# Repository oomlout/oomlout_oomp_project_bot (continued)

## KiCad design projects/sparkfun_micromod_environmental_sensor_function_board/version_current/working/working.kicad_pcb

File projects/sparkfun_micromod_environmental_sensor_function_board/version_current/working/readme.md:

# MicroMod_Environmental_Sensor_Function_Board by sparkfun  
This is a harvested standardized copy of a project from github.  
The original project can be found at:  
https://github.com/sparkfun/MicroMod_Environmental_Sensor_Function_Board  
Please consult that link for additional, details, files, and license information.  
Note: It was auto harvested and if the original repo had more than one board file or anything out of the ordinary the files here are likely not representative.

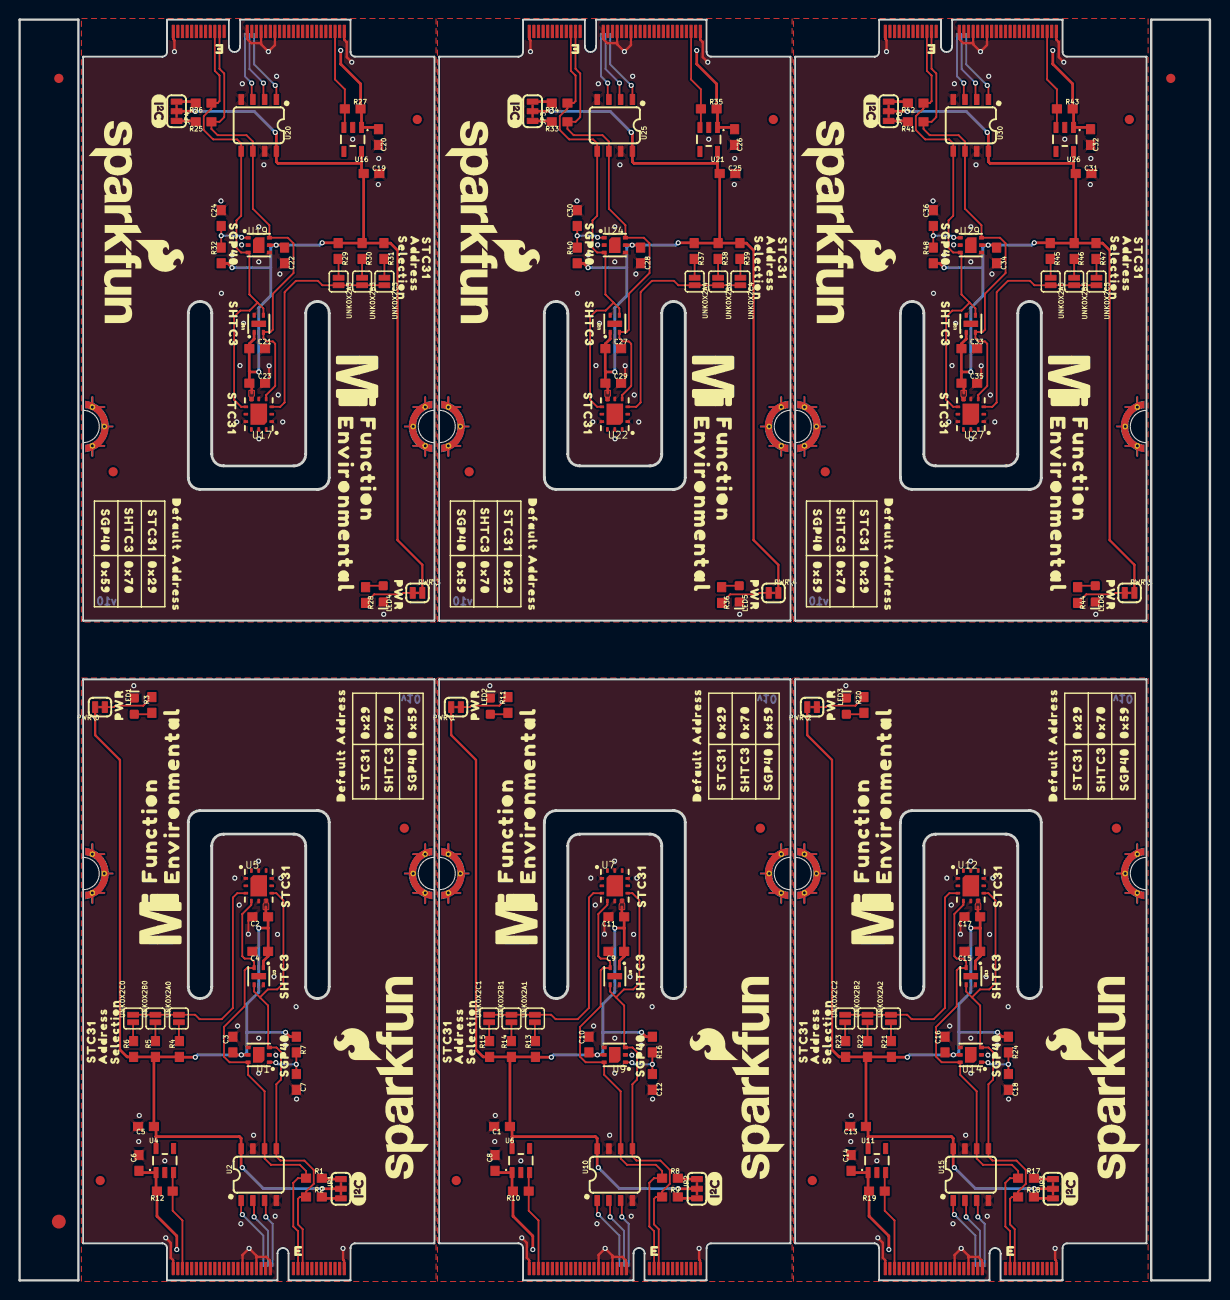
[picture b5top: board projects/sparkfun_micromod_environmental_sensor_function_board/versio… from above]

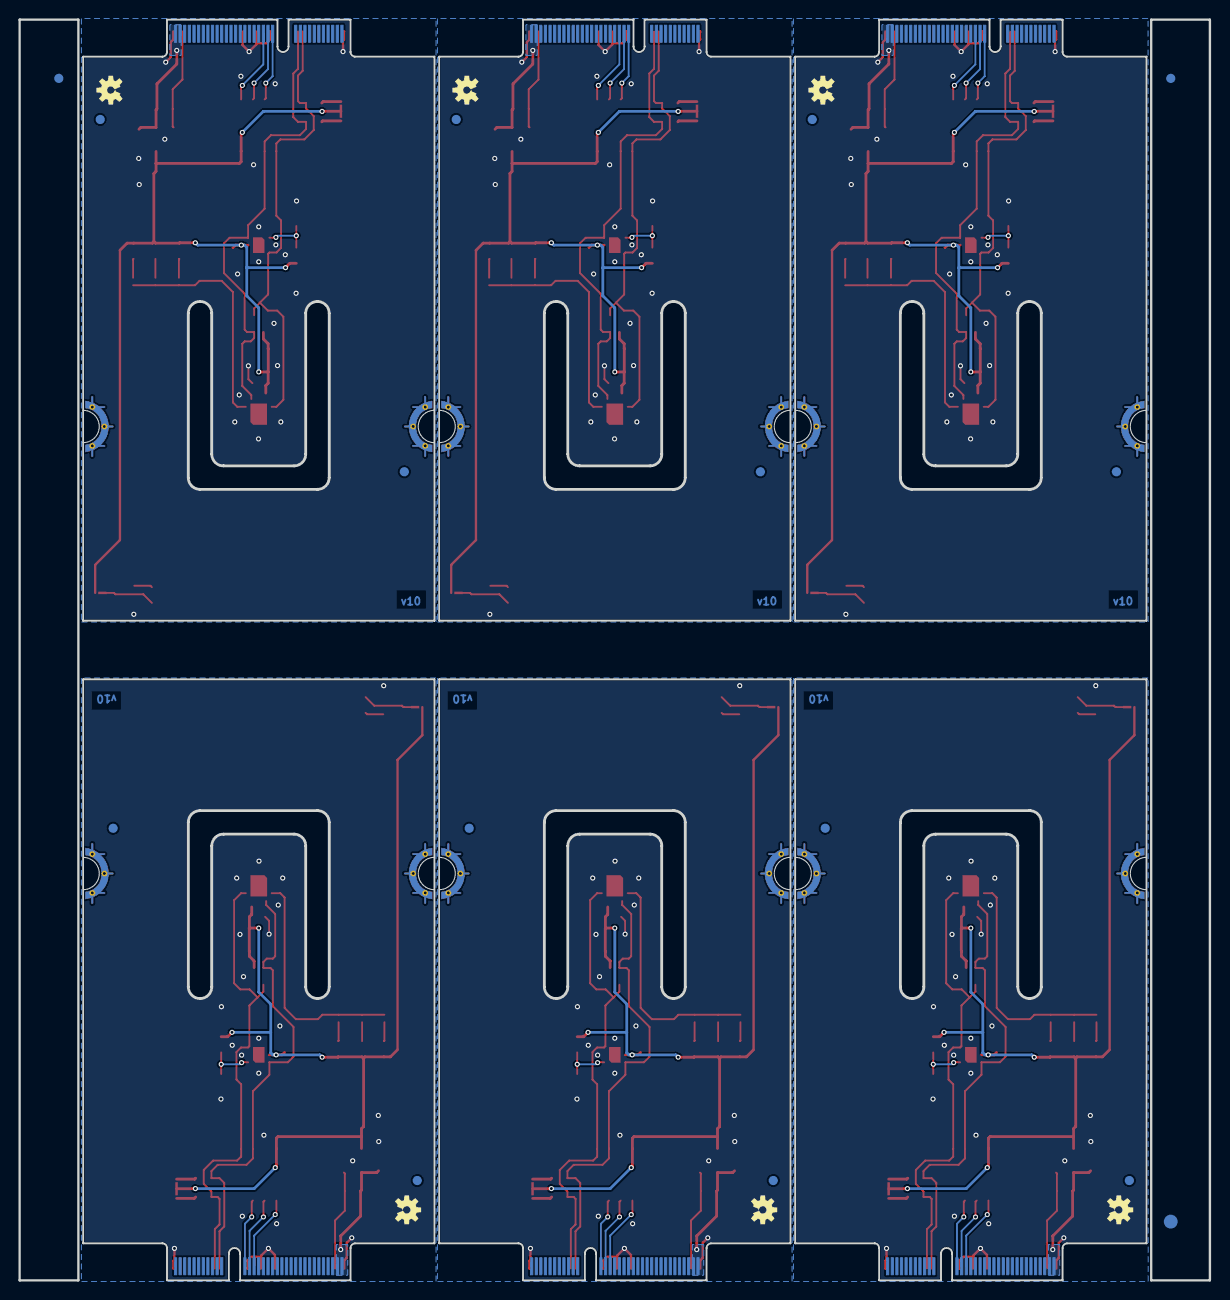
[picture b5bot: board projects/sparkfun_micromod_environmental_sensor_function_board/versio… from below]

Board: 2 copper layers, 128.7 x 136.3 mm, 330 parts (21 on the bottom side), 108 nets.

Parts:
C1, C2, C5, C6, C7, C8, C11, C12, C13, C14, C17, C18, C19, C20, C23, C24, C25, C26, C29, C30, C31, C32, C35, C36: 1.0uF; 0603
C3, C4, C9, C10, C15, C16, C21, C22, C27, C28, C33, C34: 0.1uF; 0603
E$1, E$2, E$3, E$4: FIDUCIAL-1X2
E$5, E$6: FIDUCIAL-1.5X3
FD1, FD2, FD3, FD4, FD5, FD6, FD7, FD8, FD9, FD10, FD11, FD12, FD13, FD14, FD15, FD16, FD17, FD18, FD19, FD20, FD21, FD22, FD23, FD24: FIDUCIAL1X2; FIDUCIAL-1X2
J1, J2, J3, J4, J5, J6: MICROMOD_STANDARD; M.2-CARD-E-22_FUNCTION_STANDARD
JP1, JP2, JP3, JP4, JP5, JP6: JUMPER-SMT_3_2-NC_TRACE_SILK; SMT-JUMPER_3_2-NC_TRACE_SILK
LED1, LED2, LED3, LED4, LED5, LED6: RED; LED-0603
LOGO1, LOGO3, LOGO5, LOGO7, LOGO9, LOGO11: SFE_LOGO_NAME_FLAME.2_INCH; SFE_LOGO_NAME_FLAME_.2
LOGO2, LOGO4, LOGO6, LOGO8, LOGO10, LOGO12: OSHW-LOGOS; OSHW-LOGO-S
PWR\0, PWR\1, PWR\2, PWR\3, PWR\4, PWR\5: JUMPER-SMT_2_NC_TRACE_SILK; SMT-JUMPER_2_NC_TRACE_SILK
R1, R2, R8, R9, R17, R18, R25, R26, R33, R34, R41, R42: 4.7k; 0603
R3, R6, R11, R15, R20, R23, R28, R31, R36, R39, R44, R47: 1k; 0603
R4, R13, R21, R29, R37, R45: 10k; 0603
R5, R14, R22, R30, R38, R46: 3.3k; 0603
R7, R16, R24, R32, R40, R48: 4.7; 0603
R10, R12, R19, R27, R35, R43: 100k; 0603
U1, U9, U14, U19, U24, U29: SGP40
U2, U10, U15, U20, U25, U30: EEPROM; SO08
U3, U8, U13, U18, U23, U28: SHTC3
U4, U6, U11, U16, U21, U26: 3.3V; SOT23-5
U5, U7, U12, U17, U22, U27: STC31
U$1, U$23, U$45, U$67, U$89, U$111: #0X2A#21
U$2, U$24, U$46, U$68, U$90, U$112: #0X2B#21
U$3, U$25, U$47, U$69, U$91, U$113: #0X2C#21
U$4, U$26, U$48, U$70, U$92, U$114: PWR321541
U$5, U$27, U$49, U$71, U$93, U$115: FUNCTION524
U$6, U$28, U$50, U$72, U$94, U$116: ENVIRONMENTAL526
U$7, U$29, U$51, U$73, U$95, U$117: MICROMOD_MI_LOGO_1
U$8, U$30, U$52, U$74, U$96, U$118: I2C
U$9, U$15, U$35, U$42, U$57, U$64, U$79, U$86, U$101, U$108, U$123, U$130: ADDRESS40313505
U$10, U$39, U$61, U$83, U$105, U$127: 0X2940313520
U$11, U$18, U$31, U$38, U$53, U$60, U$75, U$82, U$97, U$104, U$119, U$126: SGP40313503
U$12, U$17, U$32, U$37, U$54, U$59, U$76, U$81, U$98, U$103, U$120, U$125: SHTC3501
U$13, U$16, U$22, U$33, U$36, U$44, U$55, U$58, U$66, U$77, U$80, U$88, U$99, U$102, U$110, U$121, U$124, U$132: STC313502
U$14, U$34, U$56, U$78, U$100, U$122: DEFAULT40313504
U$19, U$40, U$62, U$84, U$106, U$128: 0X5940313520
U$20, U$41, U$63, U$85, U$107, U$129: 0X7040313520
U$21, U$43, U$65, U$87, U$109, U$131: SELECTION40313506
UNK0X2A0, UNK0X2A1, UNK0X2A2, UNK0X2A3, UNK0X2A4, UNK0X2A5, UNK0X2B0, UNK0X2B1, UNK0X2B2, UNK0X2B3, UNK0X2B4, UNK0X2B5, UNK0X2C0, UNK0X2C1, UNK0X2C2, UNK0X2C3, UNK0X2C4, UNK0X2C5: JUMPER-SMT_2_NO_SILK; SMT-JUMPER_2_NO_SILK

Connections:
3.3V: C2.1, C3.1, C4.1, C5.1, JP1.2, PWR\0.2, R4.1, R5.1, R6.1, R7.1, U1.5, U2.8, U3.1, U4.5, U5.6
3.3V1: C1.1, C9.1, C10.1, C11.1, JP2.2, PWR\1.2, R13.1, R14.1, R15.1, R16.1, U6.5, U7.6, U8.1, U9.5, U10.8
3.3V2: C13.1, C15.1, C16.1, C17.1, JP3.2, PWR\2.2, R21.1, R22.1, R23.1, R24.1, U11.5, U12.6, U13.1, U14.5, U15.8
3.3V3: C19.1, C21.1, C22.1, C23.1, JP4.2, PWR\3.2, R29.1, R30.1, R31.1, R32.1, U16.5, U17.6, U18.1, U19.5, U20.8
3.3V4: C25.1, C27.1, C28.1, C29.1, JP5.2, PWR\4.2, R37.1, R38.1, R39.1, R40.1, U21.5, U22.6, U23.1, U24.5, U25.8
3.3V5: C31.1, C33.1, C34.1, C35.1, JP6.2, PWR\5.2, R45.1, R46.1, R47.1, R48.1, U26.5, U27.6, U28.1, U29.5, U30.8
A0: J1.36, U2.1
A1: J1.34, U2.2
A2: J1.32, U2.3
A3: J2.36, U10.1
A4: J2.32, U10.3
A5: J2.34, U10.2
A6: J3.36, U15.1
A7: J3.32, U15.3
A8: J3.34, U15.2
A9: J4.36, U20.1
A10: J4.32, U20.3
A11: J4.34, U20.2
A12: J5.36, U25.1
A13: J5.32, U25.3
A14: J5.34, U25.2
A15: J6.36, U30.1
A16: J6.32, U30.3
A17: J6.34, U30.2
ADDR: U5.3, UNK0X2A0.2, UNK0X2B0.2, UNK0X2C0.2
ADDR1: U7.3, UNK0X2A1.2, UNK0X2B1.2, UNK0X2C1.2
ADDR2: U12.3, UNK0X2A2.2, UNK0X2B2.2, UNK0X2C2.2
ADDR3: U17.3, UNK0X2A3.2, UNK0X2B3.2, UNK0X2C3.2
ADDR4: U22.3, UNK0X2A4.2, UNK0X2B4.2, UNK0X2C4.2
ADDR5: U27.3, UNK0X2A5.2, UNK0X2B5.2, UNK0X2C5.2
EN: J1.71, R12.1, U4.3
EN1: J2.71, R10.1, U6.3
EN2: J3.71, R19.1, U11.3
EN3: J4.71, R27.1, U16.3
EN4: J5.71, R35.1, U21.3
EN5: J6.71, R43.1, U26.3
GND: C2.2, C3.2, C4.2, C5.2, C6.2, C7.2, J1.1, J1.33, J1.39, J1.45, J1.75, J1.GND1, J1.GND2, J1.GND3, J1.GND4, J1.GND5, J1.GND6, LED1.C, U1.2, U1.4, U1.DIEPAD, U2.4, U2.7, U3.4, U3.5, U4.2, U5.1, U5.5, U5.9, U5.11, U5.DIEPAD
GND1: C1.2, C8.2, C9.2, C10.2, C11.2, C12.2, J2.1, J2.33, J2.39, J2.45, J2.75, J2.GND1, J2.GND2, J2.GND3, J2.GND4, J2.GND5, J2.GND6, LED2.C, U6.2, U7.1, U7.5, U7.9, U7.11, U7.DIEPAD, U8.4, U8.5, U9.2, U9.4, U9.DIEPAD, U10.4, U10.7
GND2: C13.2, C14.2, C15.2, C16.2, C17.2, C18.2, J3.1, J3.33, J3.39, J3.45, J3.75, J3.GND1, J3.GND2, J3.GND3, J3.GND4, J3.GND5, J3.GND6, LED3.C, U11.2, U12.1, U12.5, U12.9, U12.11, U12.DIEPAD, U13.4, U13.5, U14.2, U14.4, U14.DIEPAD, U15.4, U15.7
GND3: C19.2, C20.2, C21.2, C22.2, C23.2, C24.2, J4.1, J4.33, J4.39, J4.45, J4.75, J4.GND1, J4.GND2, J4.GND3, J4.GND4, J4.GND5, J4.GND6, LED4.C, U16.2, U17.1, U17.5, U17.9, U17.11, U17.DIEPAD, U18.4, U18.5, U19.2, U19.4, U19.DIEPAD, U20.4, U20.7
GND4: C25.2, C26.2, C27.2, C28.2, C29.2, C30.2, J5.1, J5.33, J5.39, J5.45, J5.75, J5.GND1, J5.GND2, J5.GND3, J5.GND4, J5.GND5, J5.GND6, LED5.C, U21.2, U22.1, U22.5, U22.9, U22.11, U22.DIEPAD, U23.4, U23.5, U24.2, U24.4, U24.DIEPAD, U25.4, U25.7
GND5: C31.2, C32.2, C33.2, C34.2, C35.2, C36.2, J6.1, J6.33, J6.39, J6.45, J6.75, J6.GND1, J6.GND2, J6.GND3, J6.GND4, J6.GND5, J6.GND6, LED6.C, U26.2, U27.1, U27.5, U27.9, U27.11, U27.DIEPAD, U28.4, U28.5, U29.2, U29.4, U29.DIEPAD, U30.4, U30.7
unnamed: PWR\0.1, R3.2
unnamed: C7.1, R7.2, U1.1
unnamed: JP1.3, R1.2
unnamed: JP1.1, R2.2
unnamed: R4.2, UNK0X2A0.1
unnamed: R5.2, UNK0X2B0.1
unnamed: R6.2, UNK0X2C0.1
unnamed: LED2.A, R11.1
unnamed: PWR\1.1, R11.2
unnamed: LED1.A, R3.1
unnamed: R13.2, UNK0X2A1.1
unnamed: R14.2, UNK0X2B1.1
unnamed: R15.2, UNK0X2C1.1
unnamed: C12.1, R16.2, U9.1
unnamed: JP2.3, R8.2
unnamed: JP2.1, R9.2
unnamed: LED3.A, R20.1
unnamed: PWR\2.1, R20.2
unnamed: R21.2, UNK0X2A2.1
unnamed: R22.2, UNK0X2B2.1
unnamed: R23.2, UNK0X2C2.1
unnamed: C18.1, R24.2, U14.1
unnamed: JP3.3, R17.2
unnamed: JP3.1, R18.2
unnamed: LED4.A, R28.1
unnamed: PWR\3.1, R28.2
unnamed: R29.2, UNK0X2A3.1
unnamed: R30.2, UNK0X2B3.1
unnamed: R31.2, UNK0X2C3.1
unnamed: C24.1, R32.2, U19.1
unnamed: JP4.3, R25.2
unnamed: JP4.1, R26.2
unnamed: LED5.A, R36.1
unnamed: PWR\4.1, R36.2
unnamed: R37.2, UNK0X2A4.1
unnamed: R38.2, UNK0X2B4.1
unnamed: R39.2, UNK0X2C4.1
unnamed: C30.1, R40.2, U24.1
unnamed: JP5.3, R33.2
unnamed: JP5.1, R34.2
unnamed: LED6.A, R44.1
unnamed: PWR\5.1, R44.2
unnamed: R45.2, UNK0X2A5.1
unnamed: R46.2, UNK0X2B5.1
unnamed: R47.2, UNK0X2C5.1
unnamed: C36.1, R48.2, U29.1
unnamed: JP6.3, R41.2
unnamed: JP6.1, R42.2
SCL: J1.21, R1.1, U1.6, U2.6, U3.2, U5.4
SCL1: J2.21, R8.1, U7.4, U8.2, U9.6, U10.6
SCL2: J3.21, R17.1, U12.4, U13.2, U14.6, U15.6
SCL3: J4.21, R25.1, U17.4, U18.2, U19.6, U20.6
SCL4: J5.21, R33.1, U22.4, U23.2, U24.6, U25.6
SCL5: J6.21, R41.1, U27.4, U28.2, U29.6, U30.6
SDA: J1.19, R2.1, U1.3, U2.5, U3.3, U5.7
SDA1: J2.19, R9.1, U7.7, U8.3, U9.3, U10.5
SDA2: J3.19, R18.1, U12.7, U13.3, U14.3, U15.5
SDA3: J4.19, R26.1, U17.7, U18.3, U19.3, U20.5
SDA4: J5.19, R34.1, U22.7, U23.3, U24.3, U25.5
SDA5: J6.19, R42.1, U27.7, U28.3, U29.3, U30.5
VCC: C6.1, J1.72, J1.74, R12.2, U4.1
VCC1: C8.1, J2.72, J2.74, R10.2, U6.1
VCC2: C14.1, J3.72, J3.74, R19.2, U11.1
VCC3: C20.1, J4.72, J4.74, R27.2, U16.1
VCC4: C26.1, J5.72, J5.74, R35.2, U21.1
VCC5: C32.1, J6.72, J6.74, R43.2, U26.1

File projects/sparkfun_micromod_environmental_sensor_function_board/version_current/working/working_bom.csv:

"Id";"Designator";"Footprint";"Quantity";"Designation";"Supplier and ref";
1;"U$61,U$83,U$105,U$127,U$39,U$10";"0X2940313520";6;"";;;
2;"U$23,U$89,U$45,U$1,U$111,U$67";"#0X2A#21";6;"";;;
3;"U$95,U$51,U$29,U$7,U$73,U$117";"MICROMOD_MI_LOGO_1";6;"";;;
4;"U$38,U$97,U$31,U$119,U$75,U$11,U$60,U$126,U$18,U$53,U$82,U$104";"SGP40313503";12;"";;;
5;"R13,R45,R29,R21,R37,R4";"0603";6;"10k";;;
6;"PWR\3,PWR\1,PWR\2,PWR\5,PWR\0,PWR\4";"SMT-JUMPER_2_NC_TRACE_SILK";6;"JUMPER-SMT_2_NC_TRACE_SILK";;;
7;"U7,U27,U5,U12,U22,U17";"STC31";6;"STC31";;;
8;"FD12,FD17,FD20,FD5,FD16,FD13,FD21,FD9,FD4,FD24,FD1,FD8,FD19,FD7,FD2,FD23,FD15,FD10,FD3,FD11,FD14,FD6,FD18,FD22";"FIDUCIAL-1X2";24;"FIDUCIAL1X2";;;
9;"R25,R42,R18,R9,R1,R17,R33,R34,R2,R41,R26,R8";"0603";12;"4.7k";;;
10;"LED5,LED4,LED2,LED1,LED6,LED3";"LED-0603";6;"RED";;;
11;"R22,R46,R38,R30,R14,R5";"0603";6;"3.3k";;;
12;"C12,C25,C18,C13,C35,C7,C30,C17,C2,C23,C31,C26,C19,C6,C24,C14,C1,C36,C29,C11,C5,C20,C32,C8";"0603";24;"1.0uF";;;
13;"U$115,U$93,U$71,U$49,U$27,U$5";"FUNCTION524";6;"";;;
14;"U$58,U$80,U$22,U$55,U$88,U$44,U$121,U$33,U$102,U$36,U$124,U$13,U$132,U$66,U$110,U$77,U$99,U$16";"STC313502";18;"";;;
15;"U30,U15,U25,U2,U20,U10";"SO08";6;"EEPROM";;;
16;"U$112,U$68,U$90,U$46,U$24,U$2";"#0X2B#21";6;"";;;
17;"U$14,U$56,U$100,U$78,U$34,U$122";"DEFAULT40313504";6;"";;;
18;"U$72,U$28,U$6,U$50,U$116,U$94";"ENVIRONMENTAL526";6;"";;;
19;"U$103,U$76,U$32,U$120,U$17,U$54,U$125,U$98,U$81,U$59,U$37,U$12";"SHTC3501";12;"";;;
20;"U$9,U$123,U$15,U$86,U$35,U$57,U$108,U$130,U$42,U$79,U$101,U$64";"ADDRESS40313505";12;"";;;
21;"U4,U21,U16,U26,U11,U6";"SOT23-5";6;"3.3V";;;
22;"C4,C33,C3,C16,C10,C34,C22,C28,C15,C21,C9,C27";"0603";12;"0.1uF";;;
23;"JP1,JP4,JP2,JP6,JP5,JP3";"SMT-JUMPER_3_2-NC_TRACE_SILK";6;"JUMPER-SMT_3_2-NC_TRACE_SILK";;;
24;"UNK0X2A2,UNK0X2C4,UNK0X2A1,UNK0X2B5,UNK0X2B0,UNK0X2A5,UNK0X2A4,UNK0X2B2,UNK0X2B1,UNK0X2C1,UNK0X2C3,UNK0X2A0,UNK0X2C2,UNK0X2C0,UNK0X2B4,UNK0X2C5,UNK0X2B3,UNK0X2A3";"SMT-JUMPER_2_NO_SILK";18;"JUMPER-SMT_2_NO_SILK";;;
25;"R36,R11,R47,R28,R15,R44,R3,R31,R20,R6,R39,R23";"0603";12;"1k";;;
26;"U$30,U$74,U$52,U$8,U$118,U$96";"I2C";6;"";;;
27;"R10,R27,R35,R19,R12,R43";"0603";6;"100k";;;
28;"U$20,U$107,U$129,U$85,U$41,U$63";"0X7040313520";6;"";;;
29;"U1,U29,U9,U24,U14,U19";"SGP40";6;"SGP40";;;
30;"U$87,U$131,U$65,U$109,U$21,U$43";"SELECTION40313506";6;"";;;
31;"U3,U18,U28,U13,U8,U23";"SHTC3";6;"SHTC3";;;
32;"J1,J5,J6,J4,J2,J3";"M.2-CARD-E-22_FUNCTION_STANDARD";6;"MICROMOD_STANDARD";;;
33;"U$4,U$114,U$92,U$26,U$70,U$48";"PWR321541";6;"";;;
34;"U$47,U$3,U$25,U$113,U$69,U$91";"#0X2C#21";6;"";;;
35;"LOGO9,LOGO3,LOGO11,LOGO7,LOGO1,LOGO5";"SFE_LOGO_NAME_FLAME_.2";6;"SFE_LOGO_NAME_FLAME.2_INCH";;;
36;"R48,R40,R32,R24,R16,R7";"0603";6;"4.7";;;
37;"E$5,E$6";"FIDUCIAL-1.5X3";2;"";;;
38;"U$19,U$106,U$40,U$128,U$62,U$84";"0X5940313520";6;"";;;
39;"E$1,E$3,E$2,E$4";"FIDUCIAL-1X2";4;"";;;
40;"LOGO12,LOGO2,LOGO8,LOGO10,LOGO6,LOGO4";"OSHW-LOGO-S";6;"OSHW-LOGOS";;;

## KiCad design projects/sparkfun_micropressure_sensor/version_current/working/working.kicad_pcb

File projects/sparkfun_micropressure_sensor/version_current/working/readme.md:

# MicroPressure_Sensor by sparkfun  
This is a harvested standardized copy of a project from github.  
The original project can be found at:  
https://github.com/sparkfun/MicroPressure_Sensor  
Please consult that link for additional, details, files, and license information.  
Note: It was auto harvested and if the original repo had more than one board file or anything out of the ordinary the files here are likely not representative.

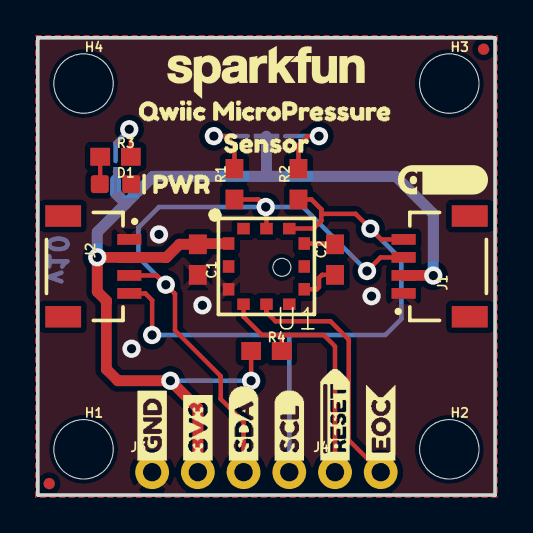
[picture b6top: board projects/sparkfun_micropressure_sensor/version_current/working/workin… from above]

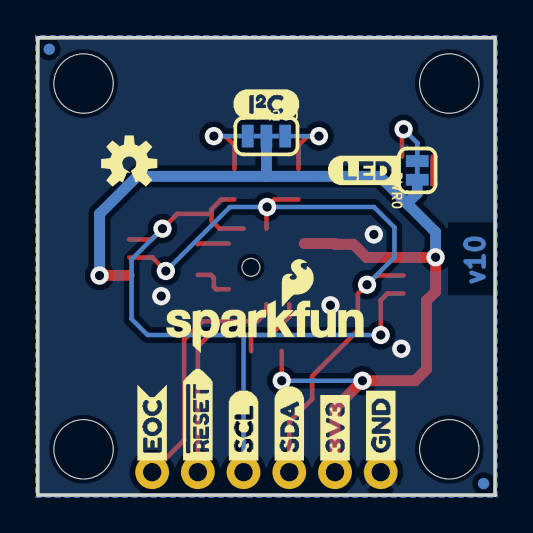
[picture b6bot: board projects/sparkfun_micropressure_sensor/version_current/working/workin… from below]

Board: 2 copper layers, 25.4 x 25.4 mm, 44 parts (14 on the bottom side), 12 nets.

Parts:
C1: 0.1uF; 0603
C2: 1nF; 0603
D1: RED; LED-0603
FD1, FD2, FD3, FD4: FIDUCIALUFIDUCIAL; FIDUCIAL-MICRO
FRAME1: FRAME-LETTER; CREATIVE_COMMONS
H1, H2, H3, H4: STAND-OFF
I2C0: SMT-JUMPER_3_2-NC_TRACE_SILK
J1, J2: Qwiic; JST04_1MM_RA
J3: 1X04_NO_SILK
J4: 1X02_NO_SILK
LOGO1: QWIIC_LOGO_5MM; QWIIC_5MM
LOGO2: OSHW-LOGOS; OSHW-LOGO-S
LOGO3: SFE_LOGO_NAME_FLAME.1_INCH; SFE_LOGO_NAME_FLAME_.1
PWR0: SMT-JUMPER_2_NC_TRACE_SILK
R1, R2, R4: 2.2k; 0603
R3: 1k; 0603
U1: MPR Series; MPR_SERIES_PRESSURE_I2C
U$1, U$15: GND1
U$2, U$14: 3V30
U$3, U$13: SDA2
U$4, U$12: SCL3
U$5, U$11: #RESET4
U$6, U$10: EOC5
U$7: PWR0
U$8: LED7
U$9: I#C0
U$16: QWIIC_MICROPRESSURE0
U$18: SENSOR2
U$19: SFE_LOGO_NAME_.1

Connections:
3.3V: C1.1, I2C0.2, J1.2, J2.2, J3.2, PWR0.1, R4.1, U1.12
EOC: J4.2, U1.8
GND: C1.2, D1.C, J1.1, J2.1, J3.1, U1.10
unnamed: PWR0.2, R3.2
unnamed: D1.A, R3.1
unnamed: I2C0.1, R2.2
unnamed: I2C0.3, R1.2
unnamed: C2.2, U1.4
unnamed: C2.1, U1.6
SCL: J1.4, J2.4, J3.4, R2.1, U1.3
SDA: J1.3, J2.3, J3.3, R1.1, U1.2
~RESET: J4.1, R4.2, U1.9

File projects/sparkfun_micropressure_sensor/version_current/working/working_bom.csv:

Row,Description,Part,References,Value,Footprint,Quantity Per PCB,Status,Datasheet
1,,1.0NF/1000PF-0603-50V-10%,C2,1nF,0603,1, ,
2,,0.1UF-0603-25V-(+80/-20%),C1,0.1UF-0603-25V-(+80/-20%),0603,1, ,
3,,LED-RED0603,D1,RED,LED-0603,1, ,
4,,FRAME-LETTER,FRAME1,FRAME-LETTER,CREATIVE_COMMONS,1, ,
5,,STAND-OFF,H1 H2 H3 H4,STAND-OFF,STAND-OFF,4, ,
6,,JUMPER-SMT_3_2-NC_TRACE_SILK,I2C0,JUMPER-SMT_3_2-NC_TRACE_SILK,SMT-JUMPER_3_2-NC_TRACE_SILK,1, ,
7,,CONN_021X02_NO_SILK,J4,CONN_021X02_NO_SILK,1X02_NO_SILK,1, ,
8,,I2C_STANDARD_NO_SILK,J3,I2C_STANDARD_NO_SILK,1X04_NO_SILK,1, ,
9,,I2C_STANDARDQWIIC,J1 J2,Qwiic,JST04_1MM_RA,2, ,
10,,OSHW-LOGOS,LOGO2,OSHW-LOGOS,OSHW-LOGO-S,1, ,
11,,QWIIC_LOGO_5MM,LOGO1,QWIIC_LOGO_5MM,QWIIC_5MM,1, ,
12,,SFE_LOGO_NAME_FLAME.1_INCH,LOGO3,SFE_LOGO_NAME_FLAME.1_INCH,SFE_LOGO_NAME_FLAME_.1,1, ,
13,,JUMPER-SMT_2_NC_TRACE_SILK,PWR0,JUMPER-SMT_2_NC_TRACE_SILK,SMT-JUMPER_2_NC_TRACE_SILK,1, ,
14,,1KOHM-0603-1/10W-1%,R3,1KOHM-0603-1/10W-1%,0603,1, ,
15,,2.2KOHM-0603-1/10W-1%,R1 R2 R4,2.2KOHM-0603-1/10W-1%,0603,3, ,
16,,MPR_SERIES_PRESSURE_I2C,U1,MPR Series,MPR_SERIES_PRESSURE_I2C,1, ,





Project info:
Schematic:,working
Variant:,default
Revision:,
Date:,2023-08-06_12-56-08
KiCad Version:,7.0.6-7.0.6~ubuntu22.04.1
Statistics:
Component Groups:,16
Component Count:,22 (0 SMD/ 0 THT)
Fitted Components:,22 (0 SMD/ 0 THT)
Number of PCBs:,1
Total Components:,22

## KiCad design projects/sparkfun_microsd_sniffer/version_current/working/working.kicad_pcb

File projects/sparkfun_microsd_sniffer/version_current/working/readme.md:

# OOMP Project  
## MicroSD_Sniffer  by sparkfun  
  
oomp key: oomp_projects_flat_sparkfun_microsd_sniffer  
(snippet of original readme)  
  
SparkFun microSD Sniffer  
=========================  

[*SparkFun microSD Sniffer (TOL-09419)*](https://www.sparkfun.com/products/9419)  

Repository Contents  
-------------------  
* **/Hardware** - Eagle design files (.brd, .sch)  
* **/Production** - Production panel files (.brd)  
  
Documentation  
--------------  
* **[Hookup Guide](https://learn.sparkfun.com/tutorials/microsd-sniffer-hookup-guide)** - Basic hookup guide for the microSD Sniffer.  

Product Versions  
----------------  
* [TOL-09419](https://www.sparkfun.com/products/9419)- Version 10  
  
License Information  
-------------------  
  
This product is _**open source**_!   
  
Please review the LICENSE.md file for license information.   
  
If you have any questions or concerns on licensing, please contact techsupport@sparkfun.com.  
  
Distributed as-is; no warranty is given.  
  
- Your friends at SparkFun.  
  
  full source readme at [readme_src.md](readme_src.md)  
  
source repo at: [https://github.com/sparkfun/MicroSD_Sniffer](https://github.com/sparkfun/MicroSD_Sniffer)  
## Board  

## Schematic  

[schematic pdf](working_schematic.pdf)  
## Images

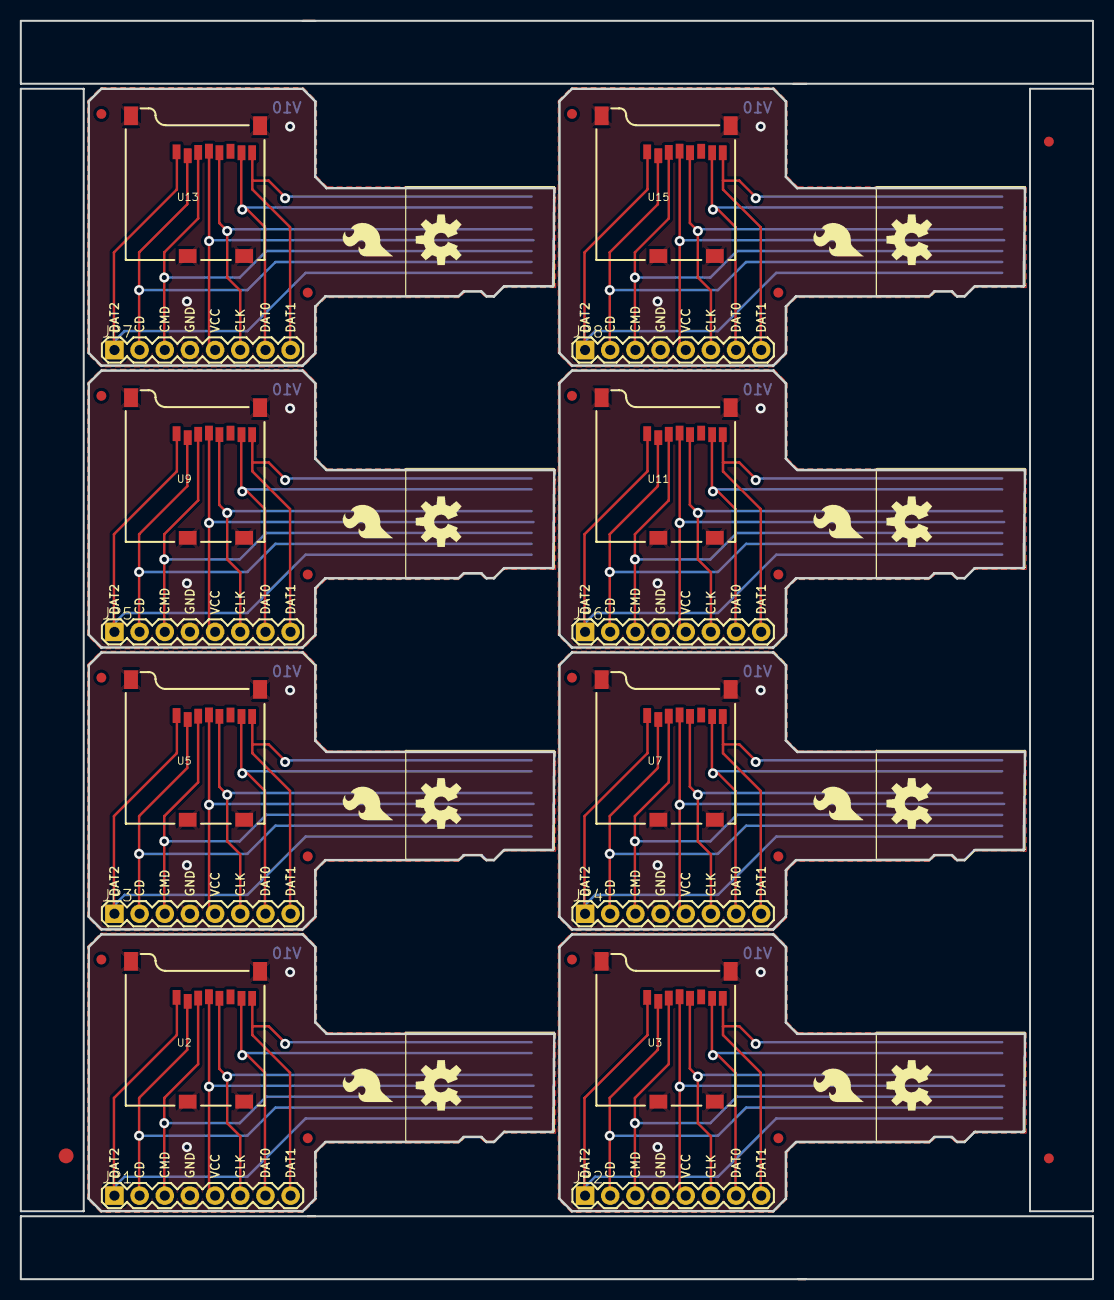
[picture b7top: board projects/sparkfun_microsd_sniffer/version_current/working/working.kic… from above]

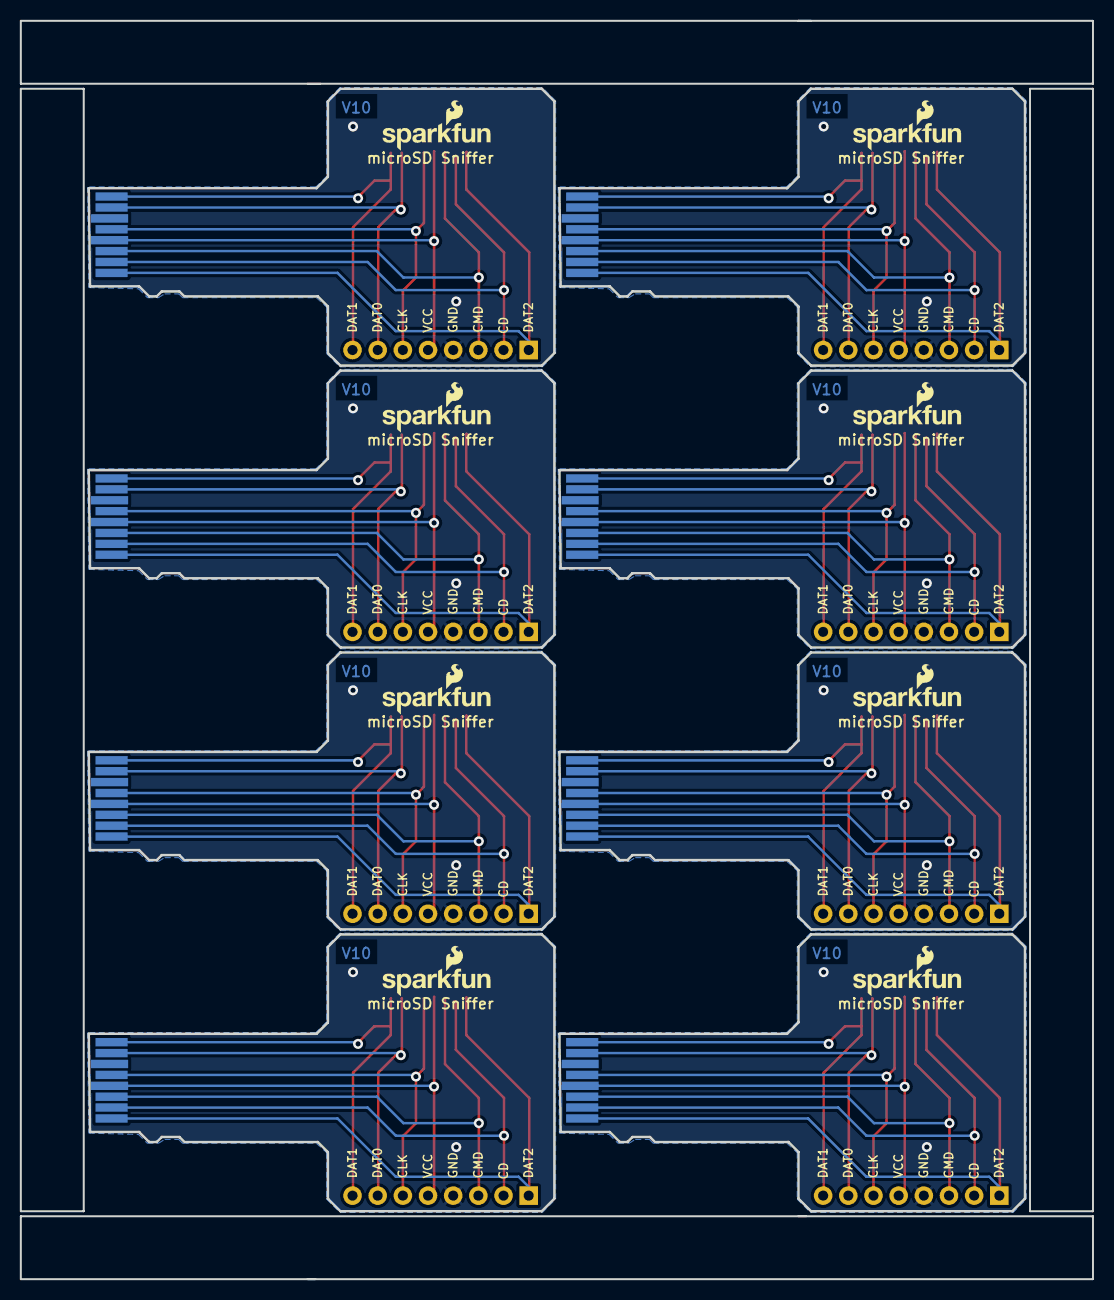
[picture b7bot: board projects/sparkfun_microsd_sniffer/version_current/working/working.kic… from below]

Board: 16 copper layers, 108.2 x 127.0 mm, 67 parts (8 on the bottom side), 64 nets.

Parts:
E$1: FIDUCIAL-1.5X3
E$4, E$8: FIDUCIAL-1X2
FID1, FID2, FID3, FID4, FID5, FID6, FID7, FID8, FID9, FID10, FID11, FID12, FID13, FID14, FID15, FID16: FIDUCIAL1X2; FIDUCIAL-1X2
JP1, JP2, JP3, JP4, JP5, JP6, JP7, JP8: 1X08
LOGO1, LOGO4, LOGO7, LOGO10, LOGO13, LOGO16, LOGO19, LOGO22: OSHW-LOGOM; OSHW-LOGO-M
LOGO2, LOGO5, LOGO8, LOGO11, LOGO14, LOGO17, LOGO20, LOGO23: SFE_LOGO_FLAME.2_INCH; SFE_LOGO_FLAME_.2
LOGO3, LOGO6, LOGO9, LOGO12, LOGO15, LOGO18, LOGO21, LOGO24: SFE_LOGO_NAME_FLAME.1_INCH; SFE_LOGO_NAME_FLAME_.1
U1, U4, U6, U8, U10, U12, U14, U16: MICRO-SDCARD
U2, U3, U5, U7, U9, U11, U13, U15: microSD Socket; MICROSD_1_1

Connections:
CD/DAT1: JP2.2, U3.2, U4.CD/DAT3
CD/DAT2: JP3.2, U5.2, U6.CD/DAT3
CD/DAT3: JP1.2, U1.CD/DAT3, U2.2
CD/DAT4: JP4.2, U7.2, U8.CD/DAT3
CD/DAT5: JP5.2, U9.2, U10.CD/DAT3
CD/DAT6: JP6.2, U11.2, U12.CD/DAT3
CD/DAT7: JP7.2, U13.2, U14.CD/DAT3
CD/DAT8: JP8.2, U15.2, U16.CD/DAT3
CLK: JP1.6, U1.CLK, U2.5
CLK1: JP2.6, U3.5, U4.CLK
CLK2: JP3.6, U5.5, U6.CLK
CLK3: JP4.6, U7.5, U8.CLK
CLK4: JP5.6, U9.5, U10.CLK
CLK5: JP6.6, U11.5, U12.CLK
CLK6: JP7.6, U13.5, U14.CLK
CLK7: JP8.6, U15.5, U16.CLK
CMD: JP1.3, U1.CMD, U2.3
CMD1: JP2.3, U3.3, U4.CMD
CMD2: JP3.3, U5.3, U6.CMD
CMD3: JP4.3, U7.3, U8.CMD
CMD4: JP5.3, U9.3, U10.CMD
CMD5: JP6.3, U11.3, U12.CMD
CMD6: JP7.3, U13.3, U14.CMD
CMD7: JP8.3, U15.3, U16.CMD
DAT0: JP1.7, U1.DAT0, U2.7
DAT1: JP1.8, U1.DAT1, U2.8
DAT2: JP1.1, U1.DAT2, U2.1
DAT3: JP2.8, U3.8, U4.DAT1
DAT4: JP2.7, U3.7, U4.DAT0
DAT5: JP2.1, U3.1, U4.DAT2
DAT6: JP3.8, U5.8, U6.DAT1
DAT7: JP3.7, U5.7, U6.DAT0
DAT8: JP3.1, U5.1, U6.DAT2
DAT9: JP4.8, U7.8, U8.DAT1
DAT10: JP4.7, U7.7, U8.DAT0
DAT11: JP4.1, U7.1, U8.DAT2
DAT12: JP5.8, U9.8, U10.DAT1
DAT13: JP5.7, U9.7, U10.DAT0
DAT14: JP5.1, U9.1, U10.DAT2
DAT15: JP6.8, U11.8, U12.DAT1
DAT16: JP6.7, U11.7, U12.DAT0
DAT17: JP6.1, U11.1, U12.DAT2
DAT18: JP7.8, U13.8, U14.DAT1
DAT19: JP7.7, U13.7, U14.DAT0
DAT20: JP7.1, U13.1, U14.DAT2
DAT21: JP8.8, U15.8, U16.DAT1
DAT22: JP8.7, U15.7, U16.DAT0
DAT23: JP8.1, U15.1, U16.DAT2
GND: JP1.4, U1.GND, U2.6, U2.CD1, U2.CD2, U2.GND1, U2.GND3
GND1: JP2.4, U3.6, U3.CD1, U3.CD2, U3.GND1, U3.GND3, U4.GND
GND2: JP3.4, U5.6, U5.CD1, U5.CD2, U5.GND1, U5.GND3, U6.GND
GND3: JP4.4, U7.6, U7.CD1, U7.CD2, U7.GND1, U7.GND3, U8.GND
GND4: JP5.4, U9.6, U9.CD1, U9.CD2, U9.GND1, U9.GND3, U10.GND
GND5: JP6.4, U11.6, U11.CD1, U11.CD2, U11.GND1, U11.GND3, U12.GND
GND6: JP7.4, U13.6, U13.CD1, U13.CD2, U13.GND1, U13.GND3, U14.GND
GND7: JP8.4, U15.6, U15.CD1, U15.CD2, U15.GND1, U15.GND3, U16.GND
VCC: JP1.5, U1.VCC, U2.4
VCC1: JP2.5, U3.4, U4.VCC
VCC2: JP3.5, U5.4, U6.VCC
VCC3: JP4.5, U7.4, U8.VCC
VCC4: JP5.5, U9.4, U10.VCC
VCC5: JP6.5, U11.4, U12.VCC
VCC6: JP7.5, U13.4, U14.VCC
VCC7: JP8.5, U15.4, U16.VCC

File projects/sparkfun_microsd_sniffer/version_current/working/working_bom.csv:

Row,Description,Part,References,Value,Footprint,Quantity Per PCB,Status,Datasheet
1,,FRAME-LETTER,FRAME1,FRAME-LETTER,CREATIVE_COMMONS,1, ,
2,,M08,JP1,M08,1X08,1, ,
3,,OSHW-LOGOM,LOGO1,OSHW-LOGOM,OSHW-LOGO-M,1, ,
4,,SFE_LOGO_FLAME.2_INCH,LOGO2,SFE_LOGO_FLAME.2_INCH,SFE_LOGO_FLAME_.2,1, ,
5,,SFE_LOGO_NAME_FLAME.1_INCH,LOGO3,SFE_LOGO_NAME_FLAME.1_INCH,SFE_LOGO_NAME_FLAME_.1,1, ,
6,,MICRO-SDCARD,U1,MICRO-SDCARD,MICRO-SDCARD,1, ,
7,,USD-SOCKET,U2,USD-SOCKET,MICROSD_1_1,1, ,





Project info:
Schematic:,working
Variant:,default
Revision:,
Date:,2023-08-06_12-56-08
KiCad Version:,7.0.6-7.0.6~ubuntu22.04.1
Statistics:
Component Groups:,7
Component Count:,7 (0 SMD/ 0 THT)
Fitted Components:,7 (0 SMD/ 0 THT)
Number of PCBs:,1
Total Components:,7
